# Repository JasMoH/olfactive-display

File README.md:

# olfactive-display
creating an olfactive display for novel HCI and olfactive art applications

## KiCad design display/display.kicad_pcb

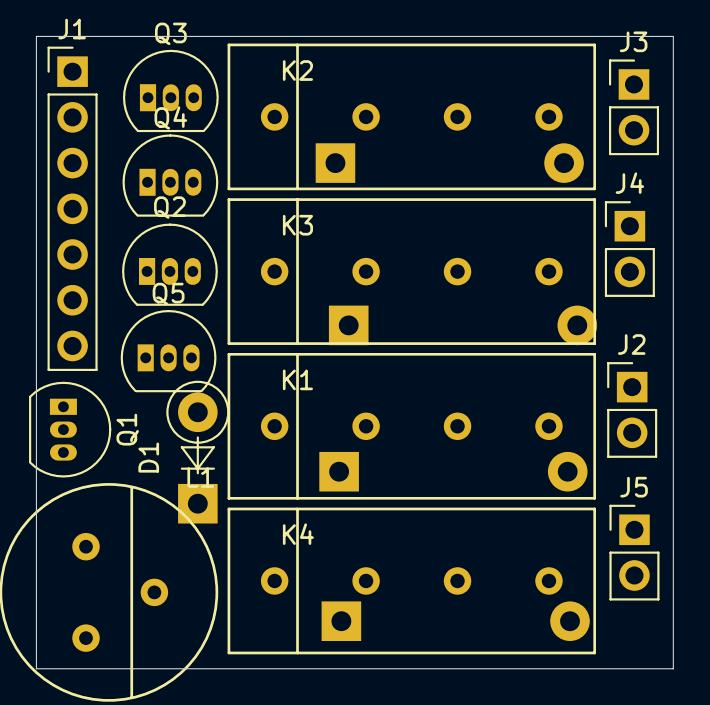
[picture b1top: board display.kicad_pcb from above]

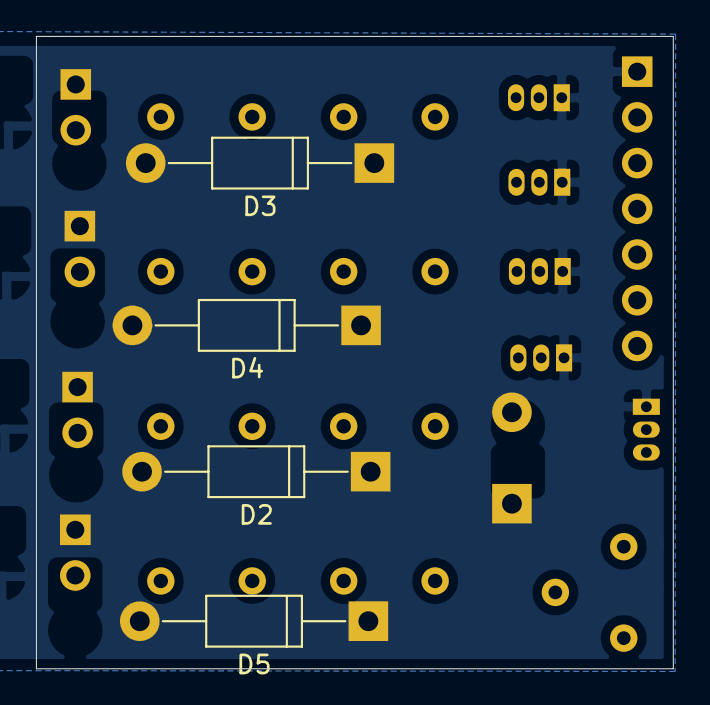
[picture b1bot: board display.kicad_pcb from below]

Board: 2 copper layers, 35.4 x 35.1 mm, 20 parts (4 on the bottom side), 18 nets, no tracks yet.

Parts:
D1: D; D_DO-41_SOD81_P5.08mm_Vertical_KathodeUp
D2, D3, D4, D5: D; D_DO-41_SOD81_P12.70mm_Horizontal
J1: Conn_01x07; Pin_Header_Straight_1x07_Pitch2.54mm
J2, J3, J4, J5: Conn_01x02_Male; Pin_Header_Straight_1x02_Pitch2.54mm
K1, K2, K3, K4: SIP-1A05; SIP-Form-A-SPST-Reed
L1: L; buzzer_coil
Q1, Q2, Q3, Q4, Q5: Q_NMOS_SGD; TO-92_Inline_Narrow_Oval

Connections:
GND: J1.1, J2.2, J3.2, J4.2, J5.2, Q1.1, Q2.1, Q3.1, Q4.1, Q5.1
unnamed: D1.1, L1.3
unnamed: D2.2, K1.3, Q2.3
unnamed: D3.2, K2.3, Q3.3
unnamed: D4.2, K3.3, Q4.3
unnamed: D5.2, K4.3, Q5.3
unnamed: J2.1, K1.4
unnamed: J3.1, K2.4
unnamed: J4.1, K3.4
unnamed: J5.1, K4.4
unnamed: L1.2, Q1.3
US-modulation: J1.6, Q1.2
US_pwr: K1.1, K2.1, K3.1, K4.1, L1.1
VCC: D1.2, D2.1, D3.1, D4.1, D5.1, J1.7, K1.2, K2.2, K3.2, K4.2
channel-1: J1.2, Q3.2
channel-2: J1.3, Q4.2
channel-3: J1.4, Q2.2
channel-4: J1.5, Q5.2

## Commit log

2019-07-01 initial schematic capture and placement for 4 channel buzzer daughter board
